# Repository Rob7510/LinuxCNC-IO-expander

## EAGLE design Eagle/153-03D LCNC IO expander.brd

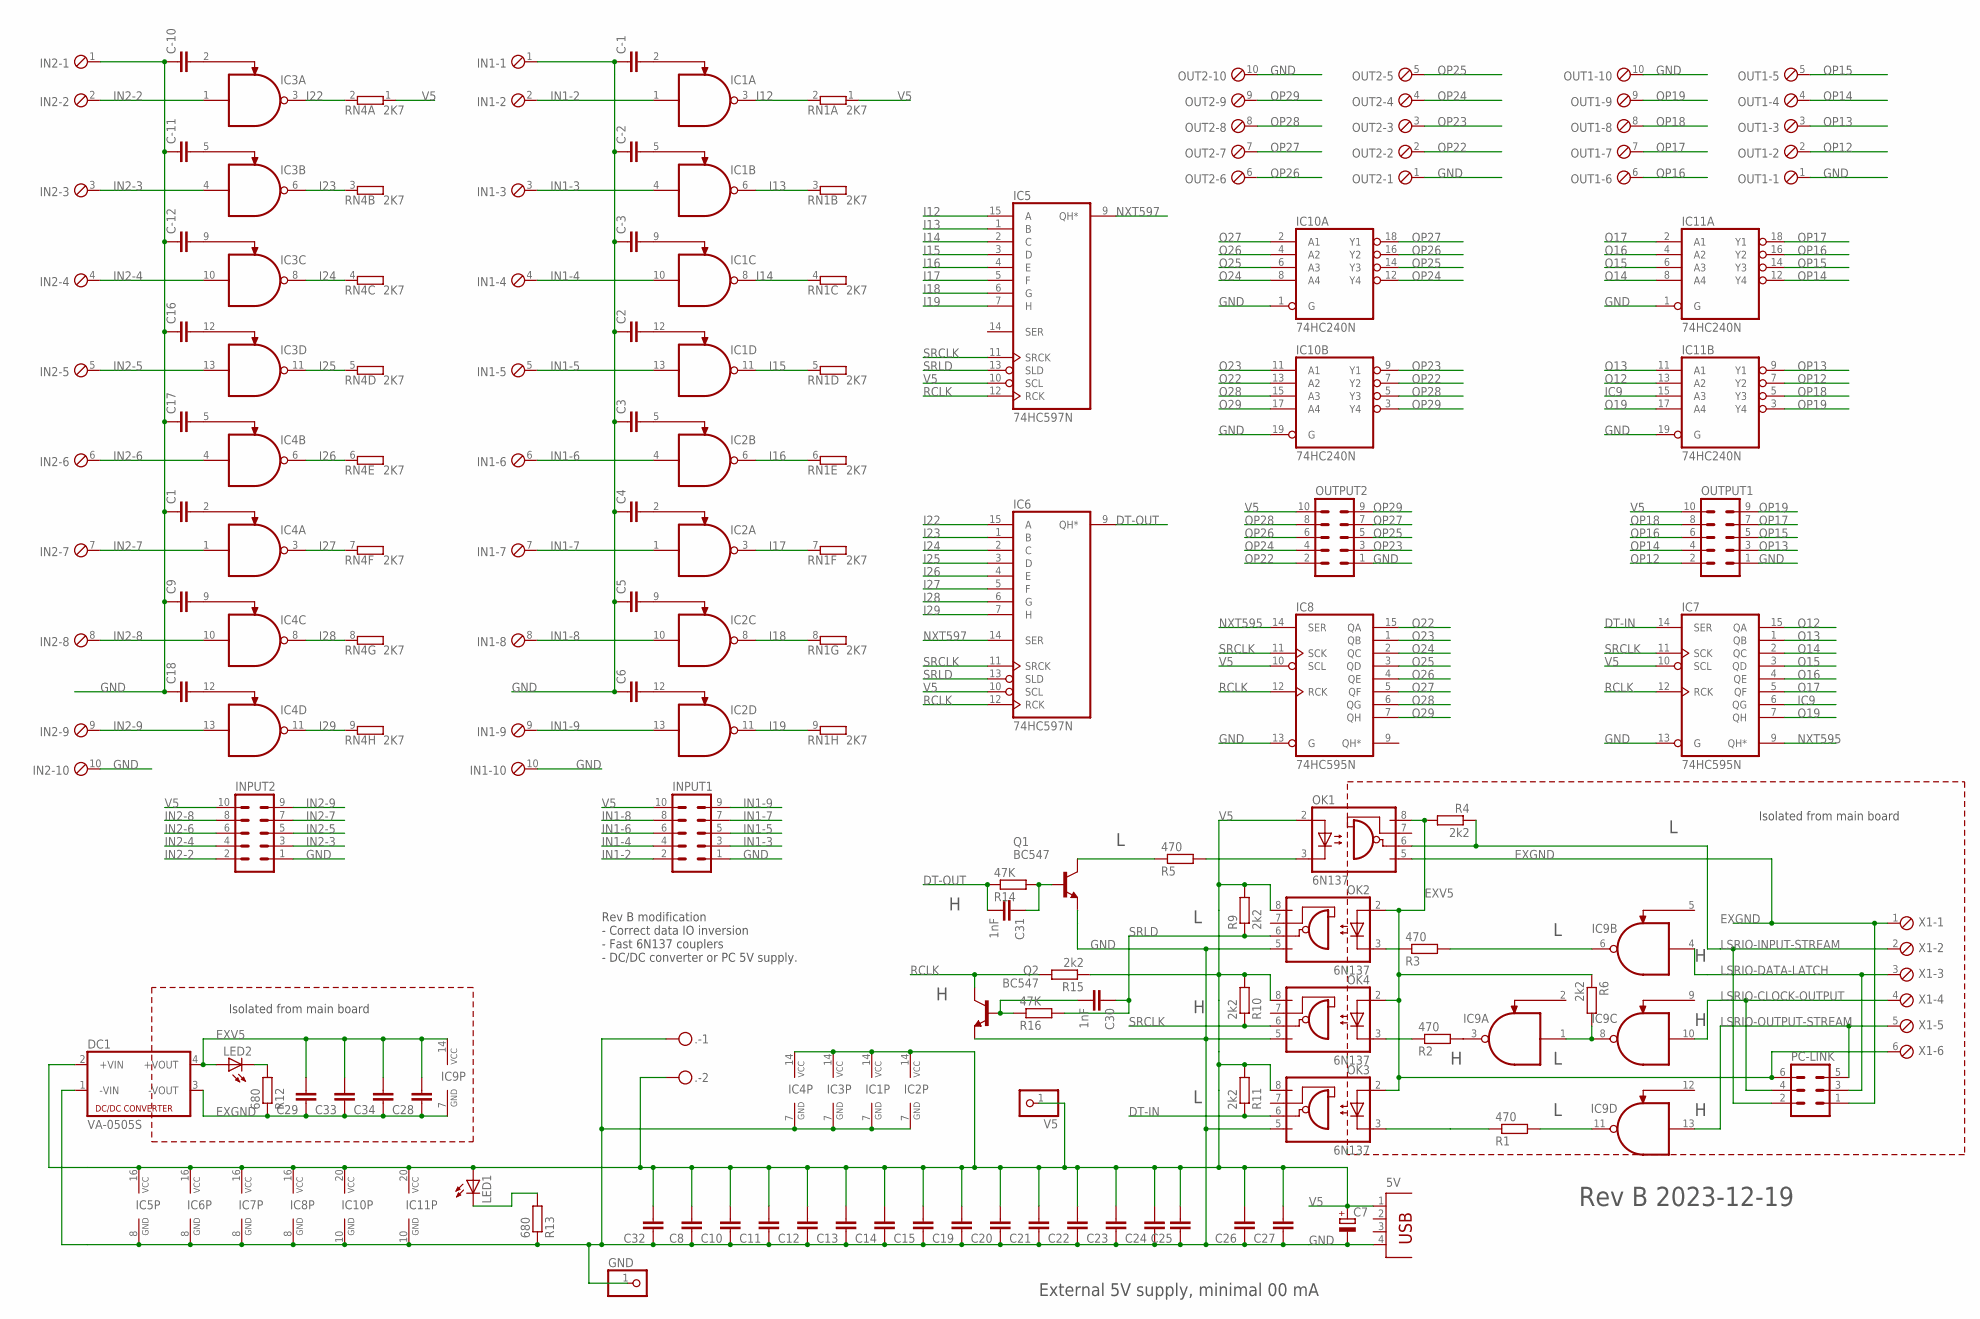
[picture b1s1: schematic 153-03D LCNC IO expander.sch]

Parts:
5V: PN87520
.: MKDSN1,5/2-5,08
C1, C2, C3, C4, C5, C6, C8, C9, C10, C11, C12, C13, C14, C15, C16, C17, C18, C19, C20, C21, C22, C23, C24, C25, C26, C27, C28, C29, C32, C33, C34: C-EU025-024X044; C025-024X044
C7: CPOL-EUE3.5-8; E3,5-8
C30, C31: 1nF; C025-024X044
C-1, C-2, C-3, C-10, C-11, C-12: C-EU025-024X044; C025-024X044
DC1: VA-0505S; 4SIL
GND: PINHD-1X1; 1X01
IC1, IC2, IC3, IC4, IC9: MC1489DIP; DIL14
IC5, IC6: 74HC597N; DIL16
IC7, IC8: 74HC595N; DIL16
IC10, IC11: 74HC240N; DIL20
IN1, IN2: MPT10; 10POL254
INPUT1, INPUT2: ML10
LED1, LED2: LED3MM
OK1, OK2, OK3, OK4: 6N137; DIL08
OUT1, OUT2: MPT10; 10POL254
OUTPUT1, OUTPUT2: ML10
PC-LINK: ML6
Q1, Q2: BC547; TO92
R1, R2, R3, R5: 470; 0207/10
R4, R6, R9, R10, R11, R15: 2k2; 0207/10
R12, R13: 680; 0207/10
R14, R16: 47K; 0207/10
RN1, RN4: 2K7; SIL9
V5: PINHD-1X1; 1X01
X1: MPT6; 6POL254

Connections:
DT-IN: IC7.14 (SER), OK3.6 (VO), R11.1
DT-OUT: C31.2, IC6.9 (QH*), R14.1
EXGND: C28.1, C29.1, C33.1, C34.1, DC1.3 (-VOUT), IC9.7 (GND), OK1.5 (GND), PC-LINK.1, R12.1, X1.1
EXV5: C28.2, C29.2, C33.2, C34.2, DC1.4 (+VOUT), IC9.14 (VCC), LED2.A, OK1.8 (VCC), OK2.2 (A), OK3.2 (A), OK4.2 (A), PC-LINK.6, R4.2, R6.1, X1.6
GND: 5V.4, ..1, C1.1, C2.1, C3.1, C4.1, C5.1, C6.1, C7.-, C8.1, C9.1, C10.1, C11.1, C12.1, C13.1, C14.1, C15.1, C16.1, C17.1, C18.1, C19.1, C20.1, C21.1, C22.1, C23.1, C24.1, C25.1, C26.1, C27.1, C32.1, C-1.1, C-2.1, C-3.1, C-10.1, C-11.1, C-12.1, DC1.1 (-VIN), GND.1, IC1.7 (GND), IC2.7 (GND), IC3.7 (GND), IC4.7 (GND), IC5.8 (GND), IC6.8 (GND), IC7.8 (GND), IC7.13 (G), IC8.8 (GND), IC8.13 (G), IC10.1 (G), IC10.10 (GND), IC10.19 (G), IC11.1 (G), IC11.10 (GND), IC11.19 (G), IN1.1, IN1.10, IN2.1, IN2.10, INPUT1.1, INPUT2.1, OK2.5 (GND), OK3.5 (GND), OK4.5 (GND), OUT1.1, OUT1.10, OUT2.1, OUT2.10, OUTPUT1.1, OUTPUT2.1, Q1.1 (E), Q2.1 (E), R13.1
I12: IC1.3 (O), IC5.15 (A), RN1.2
I13: IC1.6 (O), IC5.1 (B), RN1.3 (2)
I14: IC1.8 (O), IC5.2 (C), RN1.4 (2)
I15: IC1.11 (O), IC5.3 (D), RN1.5 (2)
I16: IC2.6 (O), IC5.4 (E), RN1.6 (2)
I17: IC2.3 (O), IC5.5 (F), RN1.7 (2)
I18: IC2.8 (O), IC5.6 (G), RN1.8 (2)
I19: IC2.11 (O), IC5.7 (H), RN1.9 (2)
I22: IC3.3 (O), IC6.15 (A), RN4.2
I23: IC3.6 (O), IC6.1 (B), RN4.3 (2)
I24: IC3.8 (O), IC6.2 (C), RN4.4 (2)
I25: IC3.11 (O), IC6.3 (D), RN4.5 (2)
I26: IC4.6 (O), IC6.4 (E), RN4.6 (2)
I27: IC4.3 (O), IC6.5 (F), RN4.7 (2)
I28: IC4.8 (O), IC6.6 (G), RN4.8 (2)
I29: IC4.11 (O), IC6.7 (H), RN4.9 (2)
IC9: IC7.6 (QG), IC11.15 (A3)
IN1-2: IC1.1 (I0), IN1.2, INPUT1.2
IN1-3: IC1.4 (I0), IN1.3, INPUT1.3
IN1-4: IC1.10 (I0), IN1.4, INPUT1.4
IN1-5: IC1.13 (I0), IN1.5, INPUT1.5
IN1-6: IC2.4 (I0), IN1.6, INPUT1.6
IN1-7: IC2.1 (I0), IN1.7, INPUT1.7
IN1-8: IC2.10 (I0), IN1.8, INPUT1.8
IN1-9: IC2.13 (I0), IN1.9, INPUT1.9
IN2-2: IC3.1 (I0), IN2.2, INPUT2.2
IN2-3: IC3.4 (I0), IN2.3, INPUT2.3
IN2-4: IC3.10 (I0), IN2.4, INPUT2.4
IN2-5: IC3.13 (I0), IN2.5, INPUT2.5
IN2-6: IC4.4 (I0), IN2.6, INPUT2.6
IN2-7: IC4.1 (I0), IN2.7, INPUT2.7
IN2-8: IC4.10 (I0), IN2.8, INPUT2.8
IN2-9: IC4.13 (I0), IN2.9, INPUT2.9
LSRIO-CLOCK-OUTPUT: IC9.10 (I0), PC-LINK.4, X1.4
LSRIO-DATA-LATCH: IC9.4 (I0), PC-LINK.3, X1.3
LSRIO-INPUT-STREAM: OK1.6 (VO), PC-LINK.2, R4.1, X1.2
LSRIO-OUTPUT-STREAM: IC9.13 (I0), PC-LINK.5, X1.5
unnamed: C-2.2, IC1.5 (I1)
unnamed: OK3.3 (C), R1.1
unnamed: C-10.2, IC3.2 (I1)
unnamed: IC9.6 (O), R3.2
unnamed: C17.2, IC4.5 (I1)
unnamed: C31.1, Q1.2 (B), R14.2
unnamed: C-3.2, IC1.9 (I1)
unnamed: IC9.11 (O), R1.2
unnamed: C30.2, Q2.2 (B), R16.1
unnamed: C1.2, IC4.2 (I1)
unnamed: C9.2, IC4.9 (I1)
unnamed: C18.2, IC4.12 (I1)
unnamed: IC9.3 (O), R2.2
unnamed: OK2.3 (C), R3.1
unnamed: Q1.3 (C), R5.1
unnamed: OK1.3 (C), R5.2
unnamed: OK4.3 (C), R2.1
unnamed: C2.2, IC1.12 (I1)
unnamed: C4.2, IC2.2 (I1)
unnamed: C5.2, IC2.9 (I1)
unnamed: C6.2, IC2.12 (I1)
unnamed: C-1.2, IC1.2 (I1)
unnamed: C3.2, IC2.5 (I1)
unnamed: IC9.1 (I0), IC9.8 (O), R6.2
unnamed: LED2.K (C), R12.2
unnamed: LED1.K (C), R13.2
unnamed: C-11.2, IC3.5 (I1)
unnamed: C-12.2, IC3.9 (I1)
unnamed: C16.2, IC3.12 (I1)
NXT595: IC7.9 (QH*), IC8.14 (SER)
NXT597: IC5.9 (QH*), IC6.14 (SER)
O12: IC7.15 (QA), IC11.13 (A2)
O13: IC7.1 (QB), IC11.11 (A1)
O14: IC7.2 (QC), IC11.8 (A4)
O15: IC7.3 (QD), IC11.6 (A3)
O16: IC7.4 (QE), IC11.4 (A2)
O17: IC7.5 (QF), IC11.2 (A1)
O19: IC7.7 (QH), IC11.17 (A4)
O22: IC8.15 (QA), IC10.13 (A2)
O23: IC8.1 (QB), IC10.11 (A1)
O24: IC8.2 (QC), IC10.8 (A4)
O25: IC8.3 (QD), IC10.6 (A3)
O26: IC8.4 (QE), IC10.4 (A2)
O27: IC8.5 (QF), IC10.2 (A1)
O28: IC8.6 (QG), IC10.15 (A3)
O29: IC8.7 (QH), IC10.17 (A4)
OP12: IC11.7 (Y2), OUT1.2, OUTPUT1.2
OP13: IC11.9 (Y1), OUT1.3, OUTPUT1.3
OP14: IC11.12 (Y4), OUT1.4, OUTPUT1.4
OP15: IC11.14 (Y3), OUT1.5, OUTPUT1.5
OP16: IC11.16 (Y2), OUT1.6, OUTPUT1.6
OP17: IC11.18 (Y1), OUT1.7, OUTPUT1.7
OP18: IC11.5 (Y3), OUT1.8, OUTPUT1.8
OP19: IC11.3 (Y4), OUT1.9, OUTPUT1.9
OP22: IC10.7 (Y2), OUT2.2, OUTPUT2.2
OP23: IC10.9 (Y1), OUT2.3, OUTPUT2.3
OP24: IC10.12 (Y4), OUT2.4, OUTPUT2.4
OP25: IC10.14 (Y3), OUT2.5, OUTPUT2.5
OP26: IC10.16 (Y2), OUT2.6, OUTPUT2.6
OP27: IC10.18 (Y1), OUT2.7, OUTPUT2.7
OP28: IC10.5 (Y3), OUT2.8, OUTPUT2.8
OP29: IC10.3 (Y4), OUT2.9, OUTPUT2.9
RCLK: IC5.12 (RCK), IC6.12 (RCK), IC7.12 (RCK), IC8.12 (RCK), Q2.3 (C), R15.2
SRCLK: IC5.11 (SRCK), IC6.11 (SRCK), IC7.11 (SCK), IC8.11 (SCK), OK4.6 (VO), R10.1
SRLD: C30.1, IC5.13 (SLD), IC6.13 (SLD), OK2.6 (VO), R9.1, R16.2
V5: 5V.1, ..2, C7.+, C8.2, C10.2, C11.2, C12.2, C13.2, C14.2, C15.2, C19.2, C20.2, C21.2, C22.2, C23.2, C24.2, C25.2, C26.2, C27.2, C32.2, DC1.2 (+VIN), IC1.14 (VCC), IC2.14 (VCC), IC3.14 (VCC), IC4.14 (VCC), IC5.10 (SCL), IC5.16 (VCC), IC6.10 (SCL), IC6.16 (VCC), IC7.10 (SCL), IC7.16 (VCC), IC8.10 (SCL), IC8.16 (VCC), IC10.20 (VCC), IC11.20 (VCC), INPUT1.10, INPUT2.10, LED1.A, OK1.2 (A), OK2.8 (VCC), OK3.8 (VCC), OK4.8 (VCC), OUTPUT1.10, OUTPUT2.10, R9.2, R10.2, R11.2, R15.1, RN1.1, RN4.1, V5.1

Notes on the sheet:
Isolated from main board
Rev B 2023-12-19
Rev B modification - Correct data IO inversion - Fast 6N137 couplers - DC/DC converter or PC 5V supply.
External 5V supply, minimal 00 mA

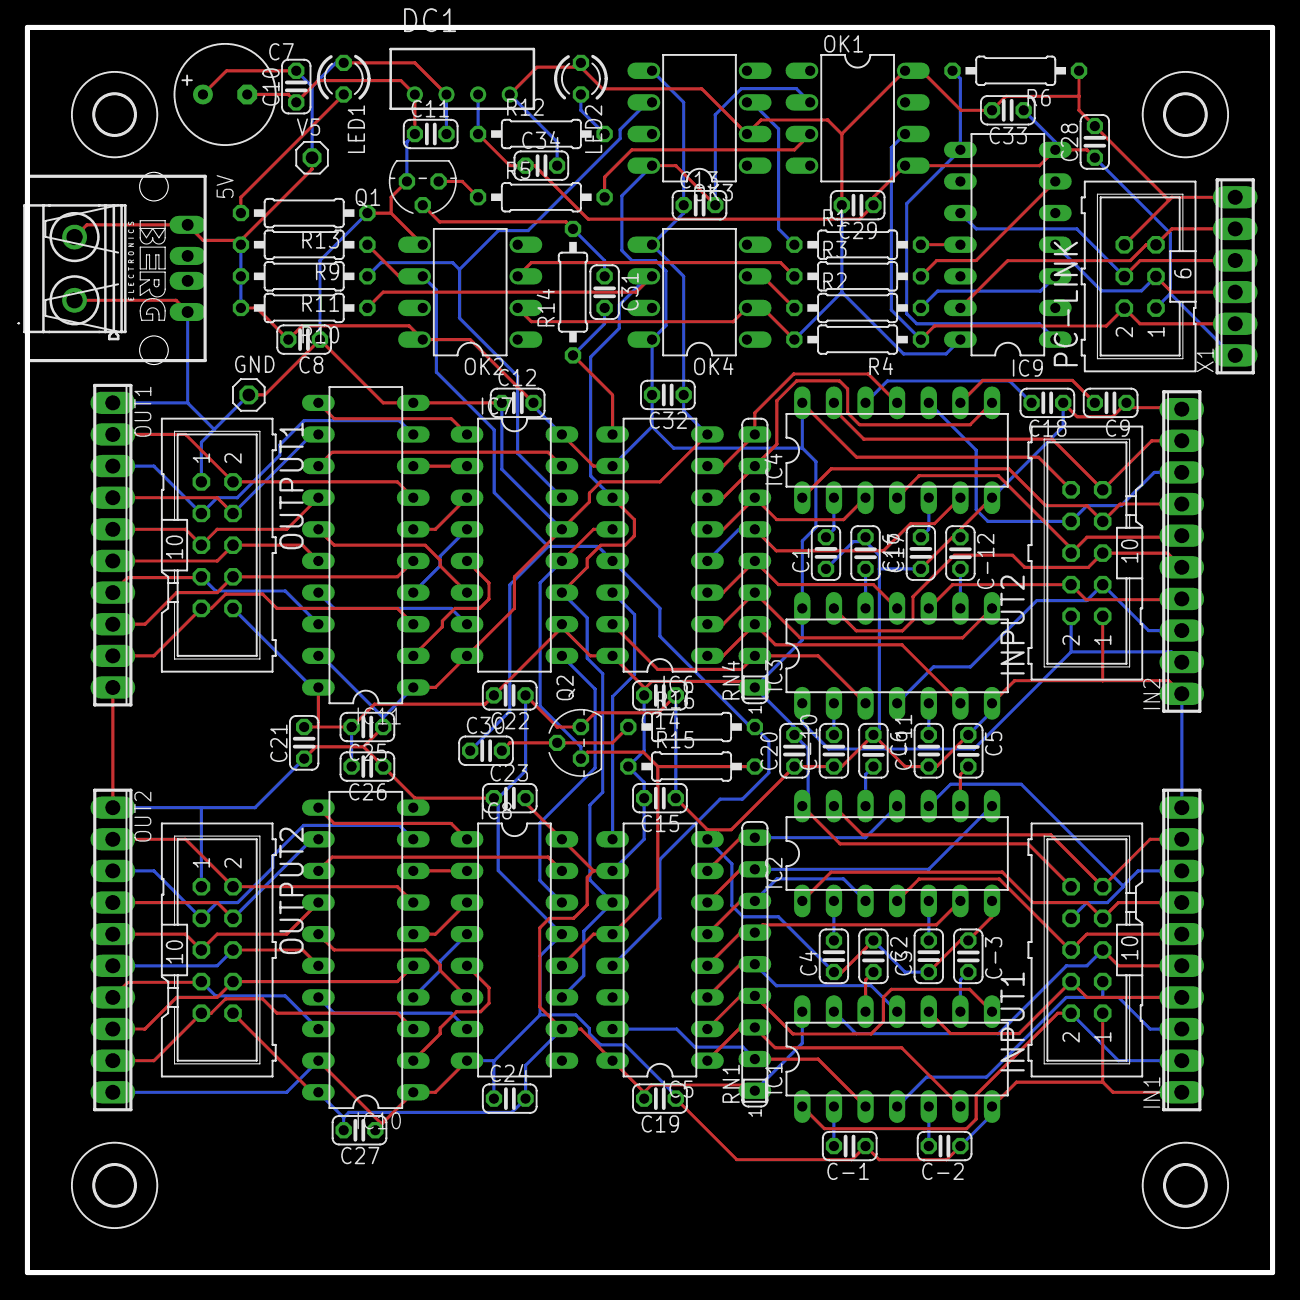
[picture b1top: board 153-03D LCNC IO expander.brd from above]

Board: 2 copper layers, 100.0 x 100.0 mm, 94 parts (0 on the bottom side), 108 nets.

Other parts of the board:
U$1, U$2, U$3, U$4: 3,2

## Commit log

2024-10-04 added lsrio16 basic setup
2024-10-04 updated lsrio16 basic setup

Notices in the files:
Eagle/153-03D LCNC IO expander.brd:
License: CERN-OHL-P V2 info@virtualsilicon.ch
